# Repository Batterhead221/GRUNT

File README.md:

# GRUNT

USB-powered ESP32-S3 sender node for HIVE outlet/circuit heartbeat monitoring.

GRUNT is a small plug-in sender board built around a Seeed Studio XIAO ESP32-S3. It plugs into a USB wall adapter through a USB-A male connector and sends periodic ESP-NOW heartbeat packets to the HIVE gateway.

If the outlet has power, GRUNT sends heartbeats.  
If the outlet loses power, GRUNT shuts off and HIVE marks that node as missing/offline.

## Project Status

Prototype hardware designed. Firmware proof-of-concept working on XIAO ESP32-S3.

## System Role

```text
Wall outlet
    ↓
USB wall adapter
    ↓
GRUNT sender board
    ↓ ESP-NOW heartbeat
HIVE gateway
```

## Hardware

Main parts:

- Seeed Studio XIAO ESP32-S3
- USB-A male plug for wall adapter power
- Power indicator LED
- Current-limiting resistor
- Mounting holes
- Simple 2-layer carrier PCB

## Power

GRUNT is powered from USB 5V.

```text
USB-A VBUS → XIAO VBUS
USB-A GND  → XIAO GND
USB shield → GND
```

USB data lines are not used:

```text
USB D+ → NC
USB D- → NC
```

The XIAO ESP32-S3 is programmed through its onboard USB-C connector.

## Firmware Behavior

GRUNT sends a heartbeat packet over ESP-NOW at a fixed interval.

## Safety Note

GRUNT does not connect directly to mains voltage. It is powered only by a standard USB wall adapter.

## Known Notes

- The XIAO ESP32-S3 external antenna must be installed for reliable ESP-NOW range.
- The USB-A connector is power-only.
- HIVE is the receiver/gateway board.
- GRUNT is the sender/outlet node.

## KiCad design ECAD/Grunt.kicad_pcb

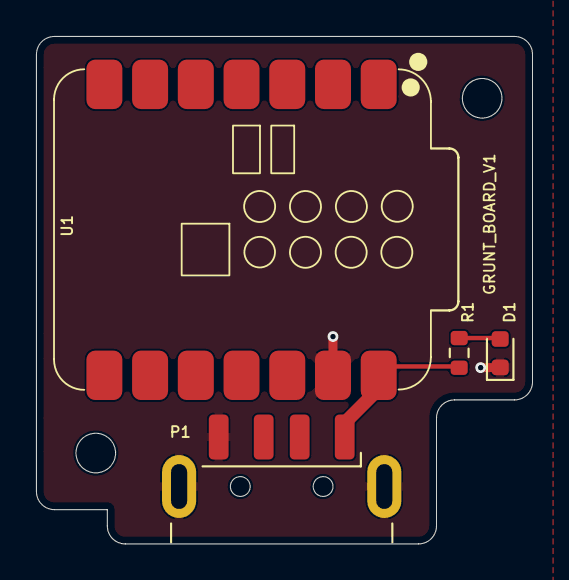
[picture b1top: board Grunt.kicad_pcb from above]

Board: 2 copper layers, 27.6 x 28.2 mm, 6 parts (0 on the bottom side), 3 nets.

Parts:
D1: LED; LED_0603_1608Metric
H1, H4: MountingHole; MountingHole_2.2mm_M2
P1: USB-A; USB_A_CNCTech_1001-011-01101_Horizontal
R1: 1K; R_0603_1608Metric
U1: XIAO-ESP32-S3; XIAO-ESP32-S3_SMD

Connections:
GND: D1.1 (K), P1.4 (GND), P1.GND, U1.13 (GND)
unnamed: D1.2 (A), R1.1
VBUS: P1.1 (VBUS), R1.2, U1.14 (VBUS)

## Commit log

2026-05-23 fixed imgs
2026-05-23 repo org
2026-05-23 readme
